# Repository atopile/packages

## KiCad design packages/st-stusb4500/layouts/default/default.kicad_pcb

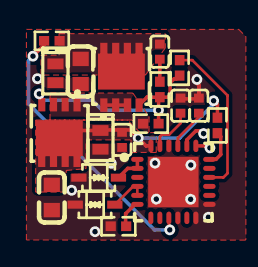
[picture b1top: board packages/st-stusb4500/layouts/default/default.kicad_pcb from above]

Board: 2 copper layers, 19 parts (0 on the bottom side), 14 nets.

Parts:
C1, C2, C3, C6: 0F; C0402
C4, C5: 0F; C0603
D1, D2: DFN1610-2_L1.6-W1.0-P1.05-RD
Q1, Q2: Vgs ℝ+V; PDFN3333-8_L3.1-W3.2-P0.65-LS3.4-BL
R1: 10000Ω; R0402
R4, R5: 1000Ω; R0402
R6: 100000Ω; R0402
R7: 22000Ω; R0402
R8: 100Ω; R0402
U1, U2: SOD-323_L1.7-W1.3-LS2.7-BI
U3: QFN-24_L4.0-W4.0-P0.50-BL-EP2.8

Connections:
DISCH: R5.2, U3.9
RESET: R1.1, U3.6
VBUS_EN_SNK: R7.2, U3.16
VBUS_VS_DISCH: R4.2, U3.18
anode: C1.2, C2.2, C3.2, C4.1, C5.1, D1.2, D2.2, R1.2, U1.1, U2.1, U3.10, U3.12, U3.13, U3.22, U3.25
cathode: U1.2, U3.1, U3.2
cc2-cathode: U2.2, U3.4, U3.5
decoupling_caps[1]-power-hv: C2.1, U3.21
gate: Q1.4, Q2.4, R6.2, R7.1, R8.1
hv: C1.1, U3.23
source: Q1.1, Q1.2, Q1.3, Q2.1, Q2.2, Q2.3, R6.1
vbus_cap-power-cathode: C3.1, C4.2, D1.1, Q2.5, Q2.6, Q2.7, Q2.8, Q2.9, R4.1, U3.24
vsink_gate_snub_c-power-cathode: C5.2, C6.2, D2.1, Q1.5, Q1.6, Q1.7, Q1.8, Q1.9, R5.1
vsink_gate_snub_c-power-hv: C6.1, R8.2

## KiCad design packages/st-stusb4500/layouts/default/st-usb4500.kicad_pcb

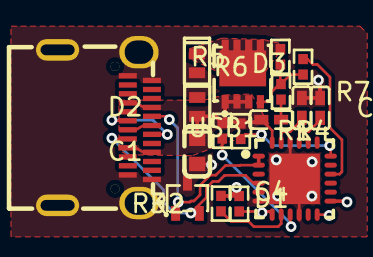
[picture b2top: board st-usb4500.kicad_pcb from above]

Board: 2 copper layers, 17 parts (0 on the bottom side), 17 nets.

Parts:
C1: 4.7µF ±10% 35V X5R; C0603
C2, C3: 1µF ±10% 16V X5R; C0402
C4: 100nF ±10% 16V X7R; C0402
D1: SOT-323-3_L2.1-W1.3-P1.32-LS2.1-BR
D2, D3: DFN1610-2_L1.6-W1.0-P1.05-RD
Q1: PDFN3333-8_L3.1-W3.2-P0.65-LS3.4-BL
R1, R4: 1kΩ ±1% 62.5mW; R0402
R2, R3: 4.7kΩ ±1% 62.5mW; R0402
R5: 100kΩ ±1% 62.5mW; R0402
R6: 22kΩ ±1% 62.5mW; R0402
R7: 100Ω ±1% 62.5mW; R0402
U1: QFN-24_L4.0-W4.0-P0.50-BL-EP2.8
USB1: USB-C-SMD_TYC-324G

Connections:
B6: USB1.A6, USB1.B6
B7: USB1.A7, USB1.B7
DISCH: R1.2, U1.9
VBUS: C1.2, C4.2, D2.1, Q1.1, Q1.2, Q1.3, R1.1, R4.1, U1.24, USB1.A4, USB1.A9, USB1.B4, USB1.B9
VBUS_EN_SNK: R6.2, U1.16
VBUS_VS_DISCH: R4.2, U1.18
drain: D3.1, Q1.5, Q1.6, Q1.7, Q1.8, Q1.9, R5.2
gate: Q1.4, R5.1, R6.1, R7.1
gnd: C1.1, C2.1, C3.1, D1.3, D2.2, D3.2, U1.6, U1.10, U1.22, U1.25, USB1.1, USB1.2, USB1.3, USB1.4, USB1.A1, USB1.A12, USB1.B1, USB1.B12
hv: R2.2, R3.2
line: R3.1, U1.8
line-1: D1.2, U1.4, U1.5, USB1.B5
line-2: D1.1, U1.1, U1.2, USB1.A5
line-3: R2.1, U1.7
pd_controller-hv: C2.2, U1.21
pd_controller-hv-1: C3.2, U1.23
pd_controller-net: C4.1, R7.2

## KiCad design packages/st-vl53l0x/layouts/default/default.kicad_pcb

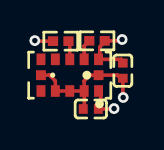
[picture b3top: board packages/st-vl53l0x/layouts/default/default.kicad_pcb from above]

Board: 2 copper layers, 5 parts (0 on the bottom side), 4 nets.

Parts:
C1, C2: 1±10.0%F; C0402
R1, R2: 10000±1.0%Ω; R0402
U1: OPTO-SMD_12P_VL53L0CXV0DH-1

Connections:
SCL: R1.2, U1.10
SDA: R2.2, U1.9
hv: C1.1, C2.1, R1.1, R2.1, U1.1, U1.11
lv: C1.2, C2.2, U1.2, U1.3, U1.4, U1.6, U1.12
